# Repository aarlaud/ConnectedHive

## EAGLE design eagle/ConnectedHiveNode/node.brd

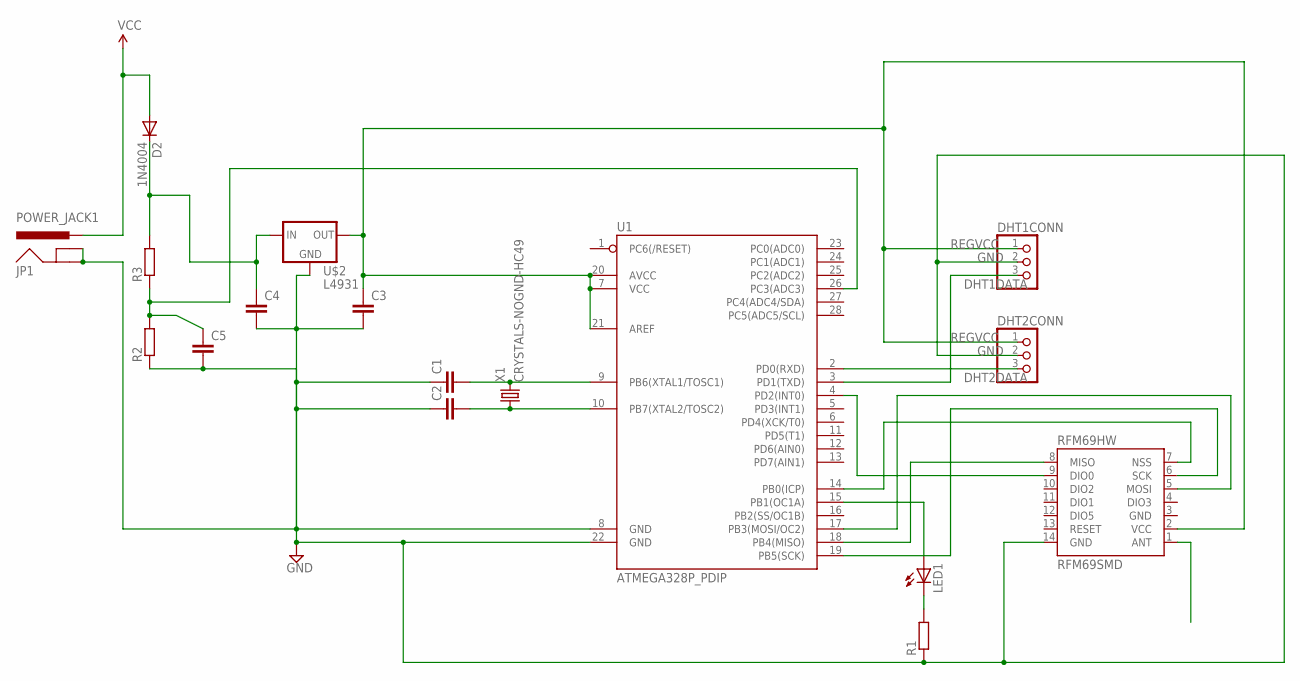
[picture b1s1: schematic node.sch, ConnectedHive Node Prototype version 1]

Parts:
C1, C2, C3, C4, C5: C-EU025-024X044; C025-024X044
D2: 1N4004; DO41-10
DHT1CONN, DHT2CONN: PINHD-1X3; 1X03
JP1: POWER_JACK1; POWER_JACK_SMD_OVERPASTE_REDBOARD_0603
LED1: LED3MM
R1, R2, R3: R-EU_0207/10; 0207/10
RFM69HW: RFM69SMD; RFM69
U1: ATMEGA328P_PDIP; DIL28-3
U$2: L4931; TO92
X1: CRYSTALS-NOGND-HC49; HC49

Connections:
DHT1DATA: DHT1CONN.3, U1.2 (PD0(RXD))
DHT2DATA: DHT2CONN.3, U1.3 (PD1(TXD))
GND: C1.1, C2.1, C3.2, C4.2, C5.2, DHT1CONN.2, DHT2CONN.2, JP1.GND (GNDBREAK), JP1.P$4 (GND), R1.1, R2.1, RFM69HW.3 (GND), RFM69HW.14 (GND), U1.8 (GND), U1.22 (GND), U$2.GND
unnamed: C1.2, U1.9 (PB6(XTAL1/TOSC1)), X1.2
unnamed: C2.2, U1.10 (PB7(XTAL2/TOSC2)), X1.1
unnamed: LED1.K (C), R1.2
unnamed: LED1.A, U1.15 (PB1(OC1A))
unnamed: C5.1, R2.2, R3.1, U1.26 (PC3(ADC3))
unnamed: RFM69HW.5 (MOSI), U1.17 (PB3(MOSI/OC2))
unnamed: RFM69HW.8 (MISO), U1.18 (PB4(MISO))
unnamed: RFM69HW.6 (SCK), U1.19 (PB5(SCK))
unnamed: RFM69HW.7 (NSS), U1.14 (PB0(ICP))
unnamed: RFM69HW.9 (DIO0), U1.4 (PD2(INT0))
REGVCC: C3.1, DHT1CONN.1, DHT2CONN.1, RFM69HW.2 (VCC), U1.7 (VCC), U1.20 (AVCC), U1.21 (AREF), U$2.OUT
RESET: RFM69HW.13 (RESET)
VCC: C4.1, D2.A, D2.C, JP1.VIN0 (PWR), R3.2, U$2.IN

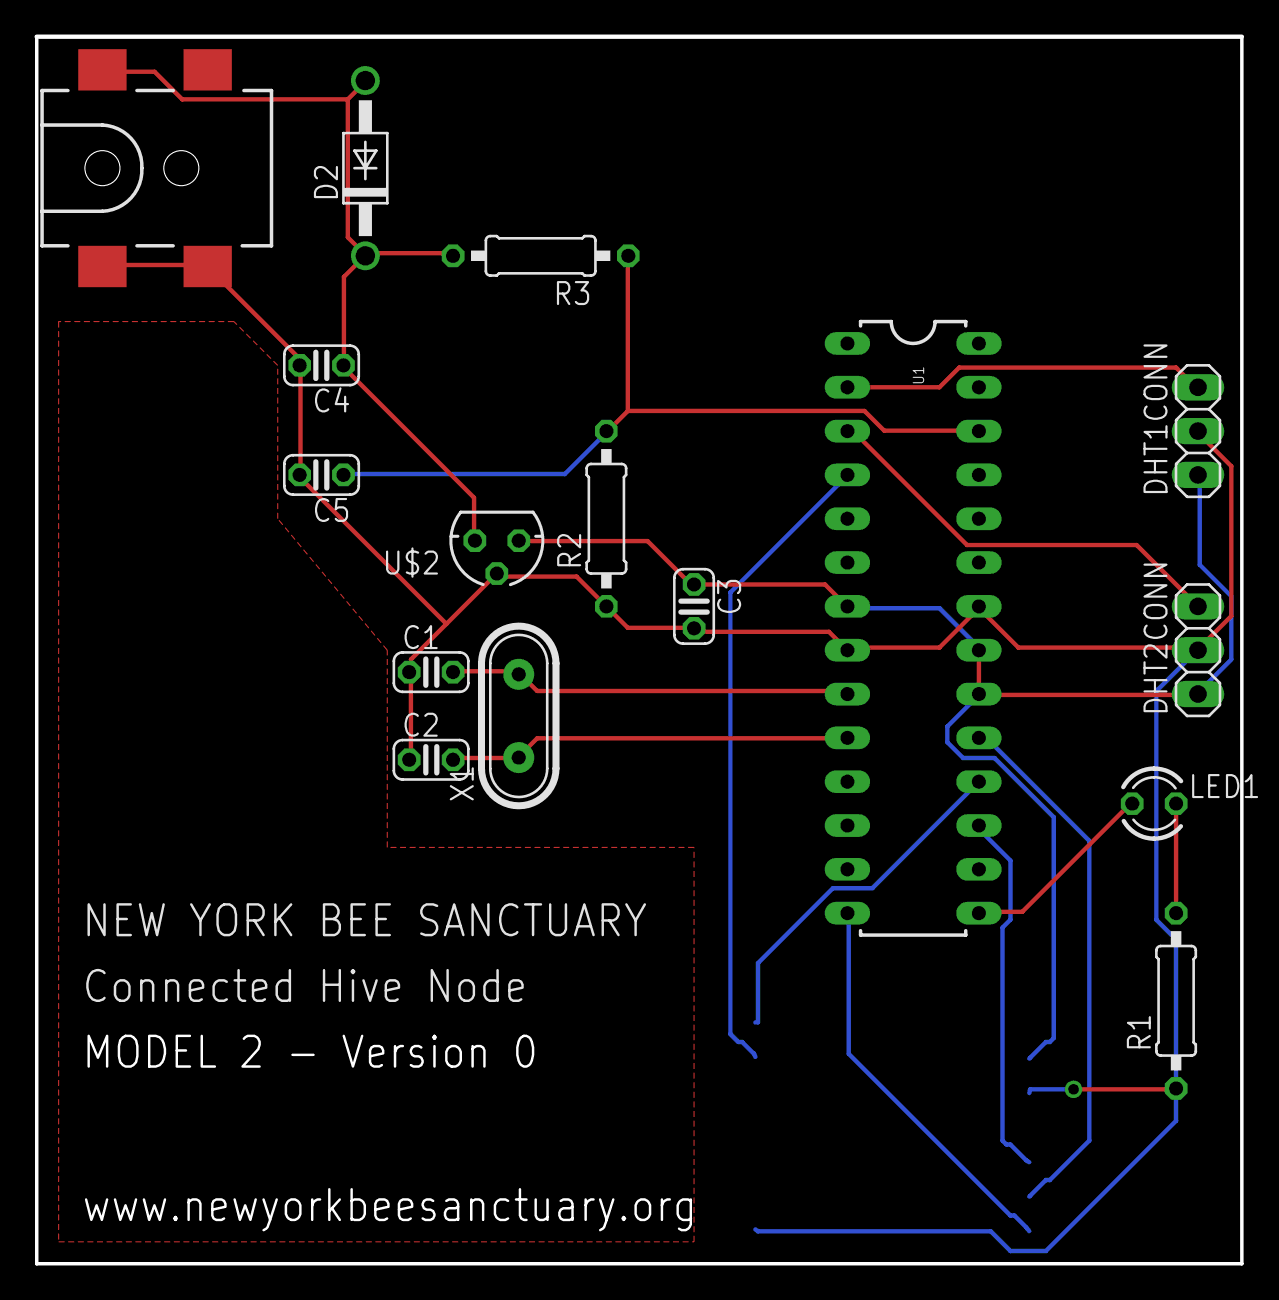
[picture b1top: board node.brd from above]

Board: 2 copper layers, 69.8 x 71.1 mm, 17 parts (1 on the bottom side), 15 nets.

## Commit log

2015-06-11 added inbound radio handling to receive ACK after sendingwithRetry requesting an ACK. Also added additional node config for multi sensors setup
2015-06-18 Added Radio LED indicator to troubleshoot radio hanging when Gateway get stuck on SendACK
2015-07-29 Added dht2 instantiation in proto2. Reduced/Removed all delays only to leave the few ms here and there for the ADC to do its part. Also put all pin to output and low to reduce power consumption
2015-07-31 Refactored DHT sensor readDHT function to read sensor directly. Will need a proper refactoring inside the library functions but good enough for prototyping and battery consumption tests. The adafruit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
2015-08-04 Adding Schematics and board for prototype version of Connected Hive Node Model 2 (2 DHT), version 0

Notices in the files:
parts and their libraries:
SparkFun-DigitalIC: Licensing: Creative Commons ShareAlike 4.0 International - https://creativecommons.org/licenses/by-sa/4.0
